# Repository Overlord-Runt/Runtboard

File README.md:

# Runtboard - The custom keyboard made by Taran Mittal/Overlord Runt
\
\
\

## What this is
The Runtboard is a custom keyboard that I designed and coded. It has 83 keys, 2 encoders, 17 LEDs, and an OLED SSD1306 screen. I designed it to have a split keyboard style with keys split down the middle but intentionally left it stuck together to have easier firmware.\
\
I spent a total of rougly 70 hours on this project, from intial designs, pcb, case, and finally firmware. Before reaching this final design, I went through about 3 different variations going back and forth with the pcb and case.\
The Runtboard has 2 layers, one with your regular keyboard layout and one that changes the functions of the encoders. I hope you like the design and you are free to make it yourself if you have a big enough 3d printer.

## Schematic
### Here are the images for my schematic
\
\
\

The header pins are there to make it easier for my wires to reach the pico without having to do funny stuff with the routing and microcontroller. It in a way gives me a third layer to use for connections, which made my life way easier when designing this board.

### The Matrix
You may notice that my matrix looks a bit funny. This is because I overcomplicated it in order to give myself an extra 2 pins to use. By removing 8 columns and adding 6 rows, I gave myself an extra 2 pins that I used to add an extra encoder.

## PCB
### Here are images for my pcb
\
\

This is what my pcb looks like. It has a basic silkscreen but i drew all of it on kicad no figma or anything.

### Silkscreen Stuff
\
\
\

On my silkscreen i have bob, the decapitated stick figure. I also have a bunch of anime references and some plugs of my socials and stuff. You should join #taran-does-stupid-things btw. its super cool. run /Darren in slack to join

## Case
I spent a lot of time designing my case(upward of 40 hours) and hope you like the design.

\

## Resources used:
Joe scotto Youtube channel\
Qmk Guides\
Ai03 plate generator\
keyboard layout editor

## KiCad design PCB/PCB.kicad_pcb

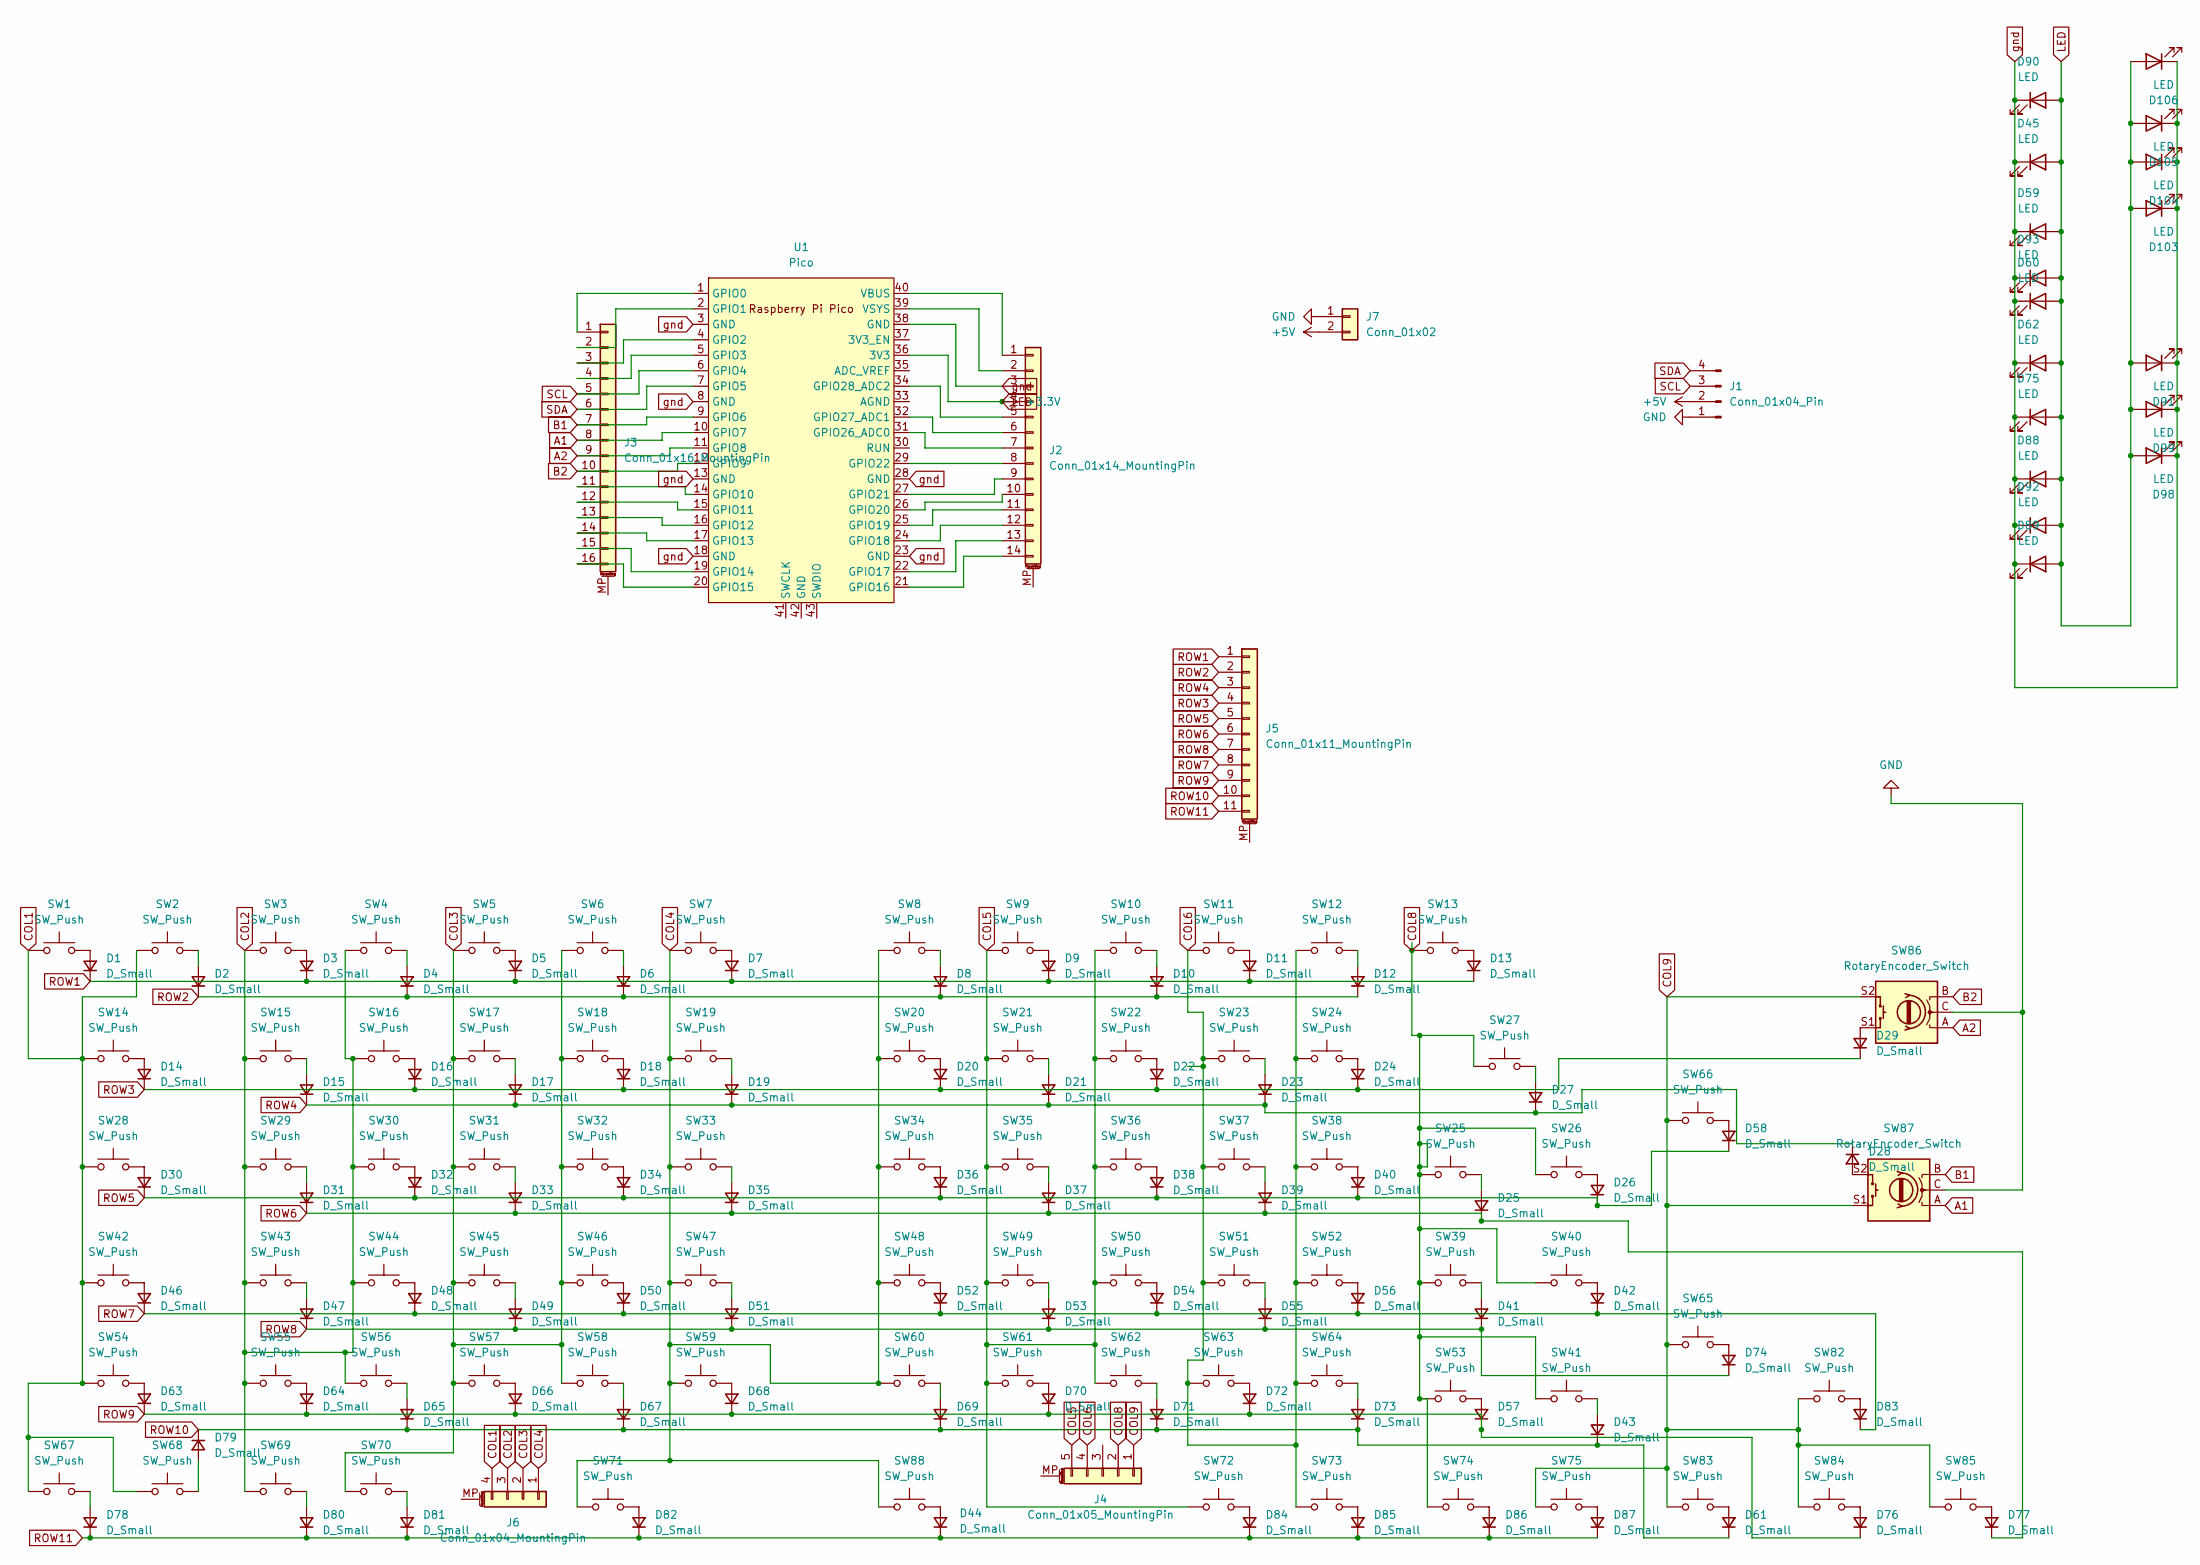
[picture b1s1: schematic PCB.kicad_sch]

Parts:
D1, D2, D3, D4, D5, D6, D7, D8, D9, D10, D11, D12, D13, D14, D15, D16, D17, D18, D19, D20, D21, D22, D23, D24, D25, D26, D27, D28, D29, D30, D31, D32, D33, D34, D35, D36, D37, D38, D39, D40, D41, D42, D43, D44, D46, D47, D48, D49, D50, D51, D52, D53, D54, D55, D56, D57, D58, D61, D63, D64, D65, D66, D67, D68, D69, D70, D71, D72, D73, D74, D76, D77, D78, D79, D80, D81, D82, D83, D84, D85, D86, D87: D_Small; DIODE-1N4148
D45, D59, D60, D62, D75, D88, D89, D90, D91, D92, D93, D98, D99, D103, D104, D105, D106: LED; LED_D5.0mm
J1: Conn_01x04_Pin; MODULE_DM-OLED096-636
J2: Conn_01x14_MountingPin; PinHeader_1x14_P2.54mm_Vertical
J3: Conn_01x16_MountingPin; PinHeader_1x16_P2.54mm_Vertical
J4: Conn_01x05_MountingPin; PinHeader_1x05_P2.54mm_Vertical
J5: Conn_01x11_MountingPin; PinHeader_1x11_P2.54mm_Vertical
J6: Conn_01x04_MountingPin; PinHeader_1x04_P2.54mm_Vertical
J7: Conn_01x02; PinSocket_1x02_P2.54mm_Vertical
SW1, SW2, SW3, SW4, SW5, SW6, SW7, SW8, SW9, SW10, SW11, SW12, SW13, SW15, SW16, SW17, SW18, SW19, SW20, SW21, SW22, SW23, SW24, SW25, SW26, SW29, SW30, SW31, SW32, SW33, SW34, SW35, SW36, SW37, SW38, SW39, SW40, SW41, SW43, SW44, SW45, SW46, SW47, SW48, SW49, SW50, SW51, SW52, SW53, SW55, SW56, SW57, SW58, SW59, SW60, SW61, SW62, SW63, SW64, SW67, SW68, SW69, SW70, SW72, SW73, SW74, SW75, SW82, SW83, SW84, SW85: SW_Push; SW_Cherry_MX_1.00u_PCB
SW14, SW27, SW28, SW42, SW54, SW65, SW66: SW_Push; SW_Cherry_MX_2.00u_PCB
SW71, SW88: SW_Push; SW_Cherry_MX_2.75u_PCB
SW86, SW87: RotaryEncoder_Switch; RotaryEncoder_Alps_EC11E-Switch_Vertical_H20mm
U1: Pico; RPi_Pico_SMD_TH

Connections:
+5V: J1.2, J7.2
A1: J3.8, SW87.A, U1.10 (GPIO7)
A2: J3.9, SW86.A, U1.11 (GPIO8)
B1: J3.7, SW87.B, U1.9 (GPIO6)
B2: J3.10, SW86.B, U1.12 (GPIO9)
COL1: J6.4, SW1.1, SW2.1, SW14.1, SW28.1, SW42.1, SW54.1, SW67.1, SW68.1
COL2: J6.3, SW3.1, SW4.1, SW15.1, SW16.1, SW29.1, SW30.1, SW43.1, SW44.1, SW55.1, SW56.1, SW69.1
COL3: J6.2, SW5.1, SW6.1, SW17.1, SW18.1, SW31.1, SW32.1, SW45.1, SW46.1, SW57.1, SW58.1, SW70.1
COL4: J6.1, SW7.1, SW8.1, SW19.1, SW20.1, SW33.1, SW34.1, SW47.1, SW48.1, SW59.1, SW60.1, SW71.1, SW88.1
COL5: J4.5, SW9.1, SW10.1, SW21.1, SW22.1, SW35.1, SW36.1, SW49.1, SW50.1, SW61.1, SW62.1, SW72.1
COL6: J4.4, SW11.1, SW12.1, SW23.1, SW24.1, SW37.1, SW38.1, SW51.1, SW52.1, SW63.1, SW64.1, SW73.1
COL8: J4.2, SW13.1, SW25.1, SW26.1, SW27.1, SW39.1, SW40.1, SW41.1, SW53.1, SW74.1
COL9: J4.1, SW65.1, SW66.1, SW75.1, SW82.1, SW83.1, SW84.1, SW85.1, SW86.S2, SW87.S1
GND: J1.1, J7.1, SW86.C, SW87.C
LED: D45.2 (A), D59.2 (A), D60.2 (A), D62.2 (A), D75.2 (A), D88.2 (A), D89.2 (A), D90.2 (A), D91.2 (A), D92.2 (A), D93.2 (A), D98.2 (A), D99.2 (A), D103.2 (A), D104.2 (A), D105.2 (A), D106.2 (A), J2.4, U1.36 (3V3)
unnamed: D1.A, SW1.2
unnamed: D2.A, SW2.2
unnamed: D3.A, SW3.2
unnamed: D4.A, SW4.2
unnamed: D5.A, SW5.2
unnamed: D6.A, SW6.2
unnamed: D7.A, SW7.2
unnamed: D8.A, SW8.2
unnamed: D9.A, SW9.2
unnamed: D10.A, SW10.2
unnamed: D11.A, SW11.2
unnamed: D12.A, SW12.2
unnamed: D13.A, SW13.2
unnamed: D14.A, SW14.2
unnamed: D15.A, SW15.2
unnamed: D16.A, SW16.2
unnamed: D17.A, SW17.2
unnamed: D18.A, SW18.2
unnamed: D19.A, SW19.2
unnamed: D20.A, SW20.2
unnamed: D21.A, SW21.2
unnamed: D22.A, SW22.2
unnamed: D23.A, SW23.2
unnamed: D24.A, SW24.2
unnamed: D25.A, SW25.2
unnamed: D26.A, SW26.2
unnamed: D27.A, SW27.2
unnamed: D28.A, SW87.S2
unnamed: D29.A, SW86.S1
unnamed: D30.A, SW28.2
unnamed: D31.A, SW29.2
unnamed: D32.A, SW30.2
unnamed: D33.A, SW31.2
unnamed: D34.A, SW32.2
unnamed: D35.A, SW33.2
unnamed: D36.A, SW34.2
unnamed: D37.A, SW35.2
unnamed: D38.A, SW36.2
unnamed: D39.A, SW37.2
unnamed: D40.A, SW38.2
unnamed: D41.A, SW39.2
unnamed: D42.A, SW40.2
unnamed: D43.A, SW41.2
unnamed: D44.A, SW88.2
unnamed: D46.A, SW42.2
unnamed: D47.A, SW43.2
unnamed: D48.A, SW44.2
unnamed: D49.A, SW45.2
unnamed: D50.A, SW46.2
unnamed: D51.A, SW47.2
unnamed: D52.A, SW48.2
unnamed: D53.A, SW49.2
unnamed: D54.A, SW50.2
unnamed: D55.A, SW51.2
unnamed: D56.A, SW52.2
unnamed: D57.A, SW53.2
unnamed: D58.A, SW66.2
unnamed: D61.A, SW83.2
unnamed: D63.A, SW54.2
unnamed: D64.A, SW55.2
unnamed: D65.A, SW56.2
unnamed: D66.A, SW57.2
unnamed: D67.A, SW58.2
unnamed: D68.A, SW59.2
unnamed: D69.A, SW60.2
unnamed: D70.A, SW61.2
unnamed: D71.A, SW62.2
unnamed: D72.A, SW63.2
unnamed: D73.A, SW64.2
unnamed: D74.A, SW65.2
unnamed: D76.A, SW84.2
unnamed: D77.A, SW85.2
unnamed: D78.A, SW67.2
unnamed: D79.A, SW68.2
unnamed: D80.A, SW69.2
unnamed: D81.A, SW70.2
unnamed: D82.A, SW71.2
unnamed: D83.A, SW82.2
unnamed: D84.A, SW72.2
unnamed: D85.A, SW73.2
unnamed: D86.A, SW74.2
unnamed: D87.A, SW75.2
unnamed: J2.1, U1.40 (VBUS)
unnamed: J2.2, U1.39 (VSYS)
unnamed: J2.5, U1.34 (GPIO28_ADC2)
unnamed: J2.6, U1.32 (GPIO27_ADC1)
unnamed: J2.7, U1.31 (GPIO26_ADC0)
unnamed: J2.8, U1.29 (GPIO22)
unnamed: J2.9, U1.27 (GPIO21)
unnamed: J2.10, U1.26 (GPIO20)
unnamed: J2.11, U1.25 (GPIO19)
unnamed: J2.12, U1.24 (GPIO18)
unnamed: J2.13, U1.22 (GPIO17)
unnamed: J2.14, U1.21 (GPIO16)
unnamed: J3.1, U1.1 (GPIO0)
unnamed: J3.2, U1.2 (GPIO1)
unnamed: J3.3, U1.4 (GPIO2)
unnamed: J3.4, U1.5 (GPIO3)
unnamed: J3.11, U1.14 (GPIO10)
unnamed: J3.12, U1.15 (GPIO11)
unnamed: J3.13, U1.16 (GPIO12)
unnamed: J3.14, U1.17 (GPIO13)
unnamed: J3.15, U1.19 (GPIO14)
unnamed: J3.16, U1.20 (GPIO15)
ROW1: D1.K, D3.K, D5.K, D7.K, D9.K, D11.K, D13.K, J5.1
ROW2: D2.K, D4.K, D6.K, D8.K, D10.K, D12.K, J5.2
ROW3: D14.K, D16.K, D18.K, D20.K, D22.K, D24.K, D29.K, J5.4
ROW4: D15.K, D17.K, D19.K, D21.K, D23.K, D27.K, D28.K, J5.3
ROW5: D26.K, D30.K, D32.K, D34.K, D36.K, D38.K, D40.K, D58.K, J5.5
ROW6: D25.K, D31.K, D33.K, D35.K, D37.K, D39.K, D77.K, J5.6
ROW7: D42.K, D46.K, D48.K, D50.K, D52.K, D54.K, D56.K, D83.K, J5.8
ROW8: D41.K, D47.K, D49.K, D51.K, D53.K, D55.K, D74.K, J5.7
ROW9: D57.K, D63.K, D64.K, D66.K, D68.K, D70.K, D72.K, D76.K, J5.9
ROW10: D43.K, D61.K, D65.K, D67.K, D69.K, D71.K, D73.K, D79.K, J5.10
ROW11: D44.K, D78.K, D80.K, D81.K, D82.K, D84.K, D85.K, D86.K, D87.K, J5.11
SCL: J1.3, J3.5, U1.6 (GPIO4)
SDA: J1.4, J3.6, U1.7 (GPIO5)
gnd: D45.1 (K), D59.1 (K), D60.1 (K), D62.1 (K), D75.1 (K), D88.1 (K), D89.1 (K), D90.1 (K), D91.1 (K), D92.1 (K), D93.1 (K), D98.1 (K), D99.1 (K), D103.1 (K), D104.1 (K), D105.1 (K), D106.1 (K), J2.3, U1.3 (GND), U1.8 (GND), U1.13 (GND), U1.18 (GND), U1.23 (GND), U1.28 (GND), U1.38 (GND)

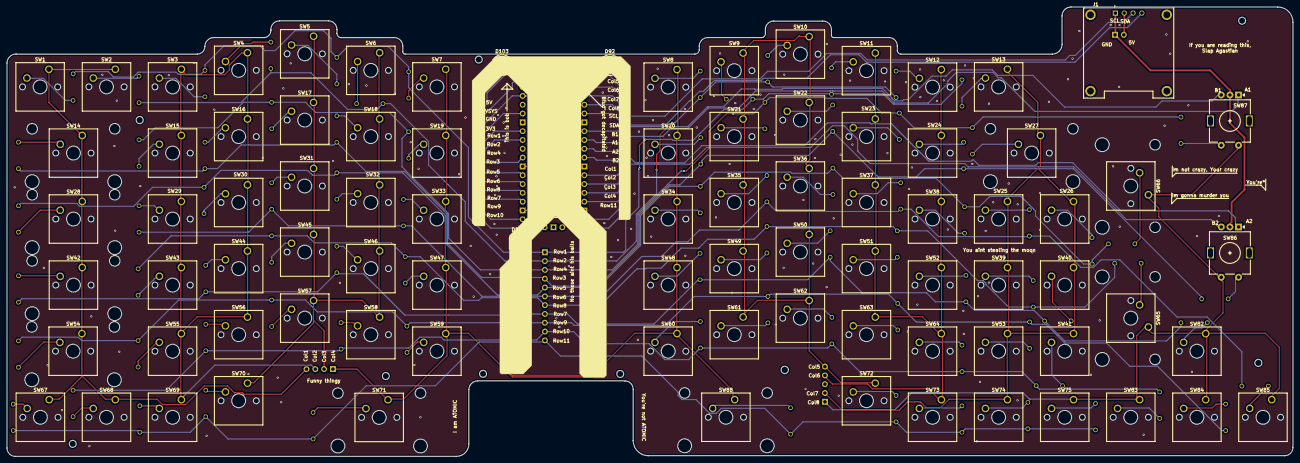
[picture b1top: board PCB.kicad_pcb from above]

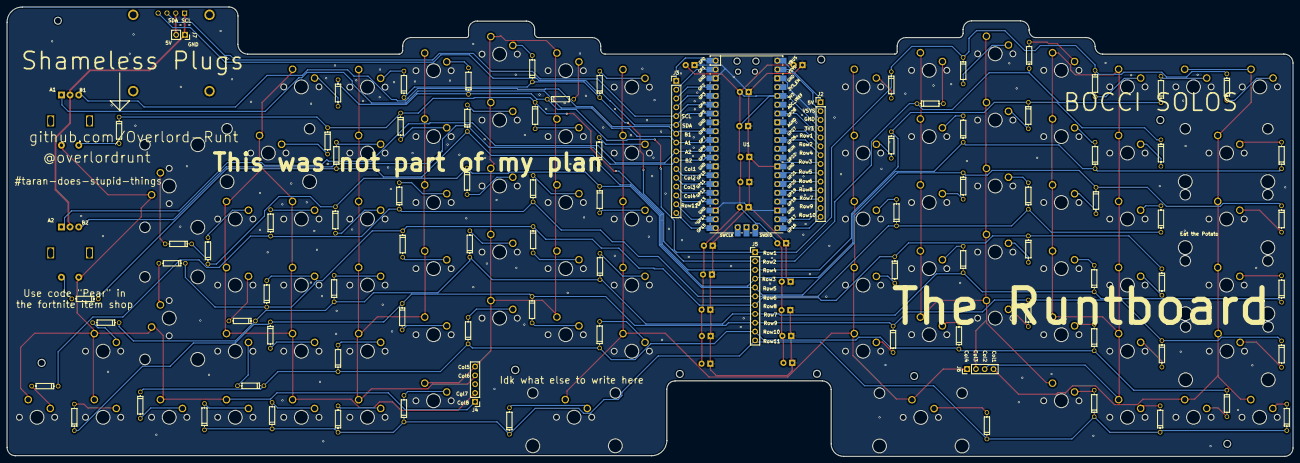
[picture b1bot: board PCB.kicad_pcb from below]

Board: 2 copper layers, 370.7 x 129.5 mm, 189 parts (89 on the bottom side), 133 nets.

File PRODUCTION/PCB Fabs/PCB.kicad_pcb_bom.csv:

Designator,Quantity,Value,Footprint,Package,MPN,DNP,Mount_Type,Description,Sim.Device,Sim.Pins
"D1, D10, D11, D12, D13, D14, D15, D16, D17, D18, D19, D2, D20, D21, D22, D23, D24, D25, D26, D27, D28, D29, D3, D30, D31, D32, D33, D34, D35, D36, D37, D38, D39, D4, D40, D41, D42, D43, D44, D46, D47, D48, D49, D5, D50, D51, D52, D53, D54, D55, D56, D57, D58, D6, D61, D63, D64, D65, D66, D67, D68, D69, D7, D70, D71, D72, D73, D74, D76, D77, D78, D79, D8, D80, D81, D82, D83, D84, D85, D86, D87, D9",82,D_Small,DIODE-1N4148,,,,tht,"Diode, small symbol",D,1=K 2=A
"D103, D104, D105, D106, D45, D59, D60, D62, D75, D88, D89, D90, D91, D92, D93, D98, D99",17,LED,LED_D5.0mm,,,,tht,Light emitting diode,,
J1,1,Conn_01x04_Pin,MODULE_DM-OLED096-636,,,,tht,"Generic connector, single row, 01x04, script generated",,
J2,1,Conn_01x14_MountingPin,PinHeader_1x14_P2.54mm_Vertical,,,,tht,"Generic connectable mounting pin connector, single row, 01x14, script generated (kicad-library-utils/schlib/autogen/connector/)",,
J3,1,Conn_01x16_MountingPin,PinHeader_1x16_P2.54mm_Vertical,,,,tht,"Generic connectable mounting pin connector, single row, 01x16, script generated (kicad-library-utils/schlib/autogen/connector/)",,
J4,1,Conn_01x05_MountingPin,PinHeader_1x05_P2.54mm_Vertical,,,,tht,"Generic connectable mounting pin connector, single row, 01x05, script generated (kicad-library-utils/schlib/autogen/connector/)",,
J5,1,Conn_01x11_MountingPin,PinHeader_1x11_P2.54mm_Vertical,,,,tht,"Generic connectable mounting pin connector, single row, 01x11, script generated (kicad-library-utils/schlib/autogen/connector/)",,
J6,1,Conn_01x04_MountingPin,PinHeader_1x04_P2.54mm_Vertical,,,,tht,"Generic connectable mounting pin connector, single row, 01x04, script generated (kicad-library-utils/schlib/autogen/connector/)",,
J7,1,Conn_01x02,PinSocket_1x02_P2.54mm_Vertical,,,,tht,"Generic connector, single row, 01x02, script generated (kicad-library-utils/schlib/autogen/connector/)",,
"SW1, SW10, SW11, SW12, SW13, SW15, SW16, SW17, SW18, SW19, SW2, SW20, SW21, SW22, SW23, SW24, SW25, SW26, SW29, SW3, SW30, SW31, SW32, SW33, SW34, SW35, SW36, SW37, SW38, SW39, SW4, SW40, SW41, SW43, SW44, SW45, SW46, SW47, SW48, SW49, SW5, SW50, SW51, SW52, SW53, SW55, SW56, SW57, SW58, SW59, SW6, SW60, SW61, SW62, SW63, SW64, SW67, SW68, SW69, SW7, SW70, SW72, SW73, SW74, SW75, SW8, SW82, SW83, SW84, SW85, SW9",71,SW_Push,SW_Cherry_MX_1.00u_PCB,,,,tht,"Push button switch, generic, two pins",,
"SW14, SW27, SW28, SW42, SW54, SW65, SW66",7,SW_Push,SW_Cherry_MX_2.00u_PCB,,,,tht,"Push button switch, generic, two pins",,
"SW71, SW88",2,SW_Push,SW_Cherry_MX_2.75u_PCB,,,,tht,"Push button switch, generic, two pins",,
"SW86, SW87",2,RotaryEncoder_Switch,RotaryEncoder_Alps_EC11E-Switch_Vertical_H20mm,,,,tht,"Rotary encoder, dual channel, incremental quadrate outputs, with switch",,
U1,1,Pico,RPi_Pico_SMD_TH,,,,tht,,,

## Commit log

2025-01-28 Update LICENSE
2025-04-14 Create CNAME
